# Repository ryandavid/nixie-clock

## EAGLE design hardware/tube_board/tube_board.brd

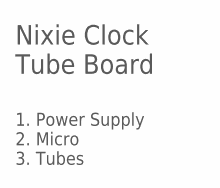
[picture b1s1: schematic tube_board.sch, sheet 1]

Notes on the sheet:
Nixie Clock Tube Board
1. Power Supply 2. Micro 3. Tubes

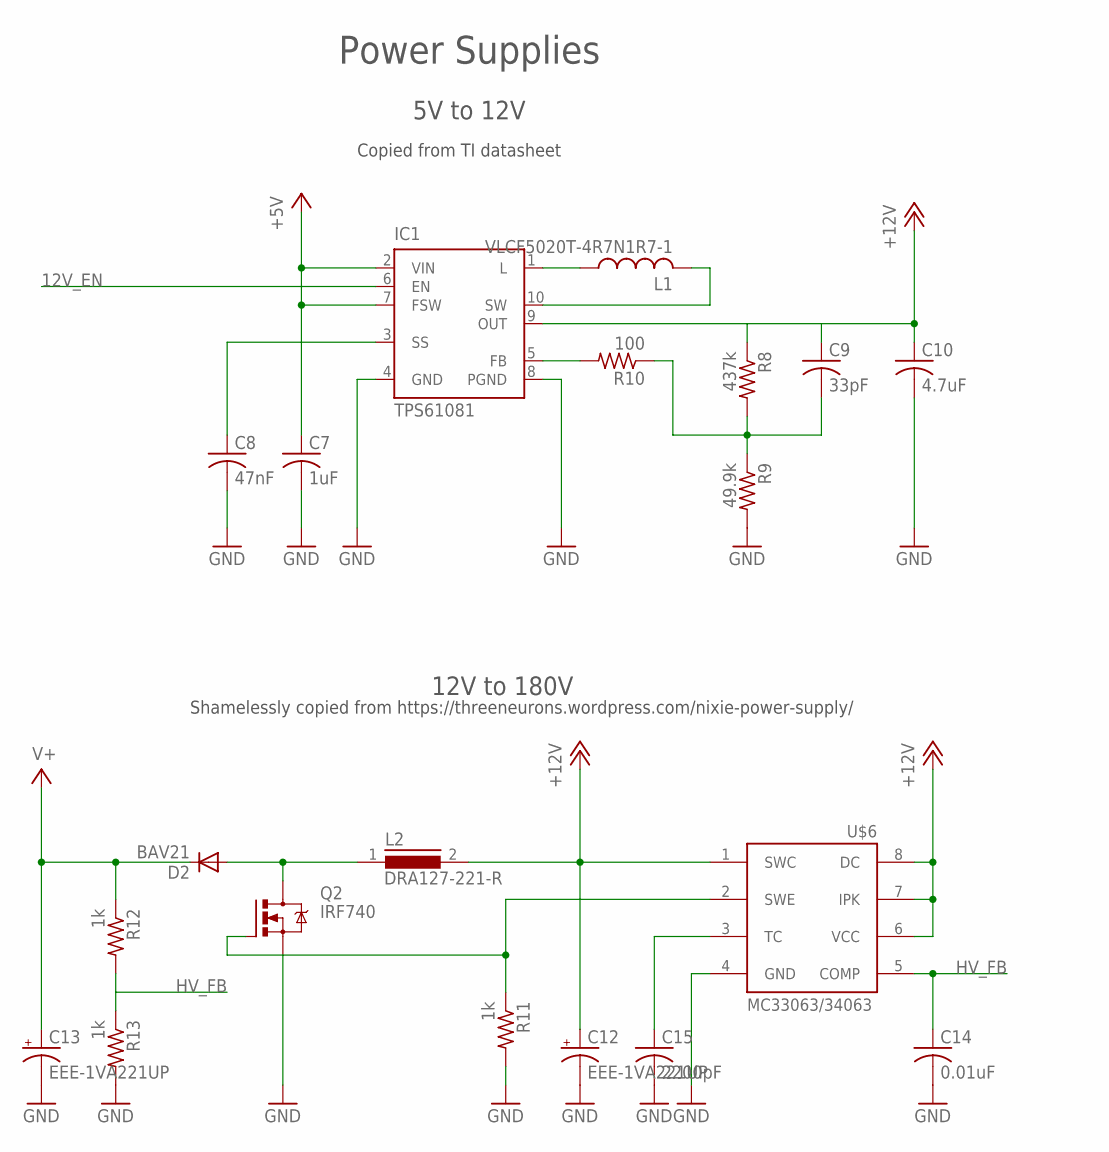
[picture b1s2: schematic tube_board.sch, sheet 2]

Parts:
C7: 1uF; C0603
C8: 47nF; C0603
C9: 33pF; C0603
C10: 4.7uF; C0603
C12, C13: EEE-1VA221UP; PANASONIC_G
C14: 0.01uF; C0603
C15: 2200pF; C0603
D2: BAV21; SOD323-R
IC1: TPS61081; S-PDSO-N10
L1: VLCF5020T-4R7N1R7-1; L5650M
L2: DRA127-221-R; DR127
Q2: IRF740; TO220BV
R8: 437k; R0603
R9: 49.9k; R0603
R10: 100; R0603
R11, R12, R13: 1k; R0603
U$6: MC34063D; SO08

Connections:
12V_EN: IC1.6 (EN); also elsewhere on the board
+5V: C7.1, IC1.2 (VIN), IC1.7 (FSW); also elsewhere on the board
+12V: C9.1, C10.1, C12.+, IC1.9 (OUT), L2.2, R8.1, U$6.1 (SWC), U$6.6 (VCC), U$6.7 (IPK), U$6.8 (DC); also elsewhere on the board
GND: C7.2, C8.2, C10.2, C12.-, C13.-, C14.2, C15.2, IC1.4 (GND), IC1.8 (PGND), Q2.S, R9.2, R11.2, R13.2, U$6.4 (GND); also elsewhere on the board
HV_FB: C14.1, R12.2, R13.1, U$6.5 (COMP)
unnamed: IC1.1 (L), L1.1
unnamed: IC1.10 (SW), L1.2
unnamed: C8.1, IC1.3 (SS)
unnamed: C9.2, R8.2, R9.1, R10.1
unnamed: D2.A, L2.1, Q2.D
unnamed: C15.1, U$6.3 (TC)
unnamed: IC1.5 (FB), R10.2
unnamed: Q2.G, R11.1, U$6.2 (SWE)
V+: C13.+, D2.C, R12.1; also elsewhere on the board

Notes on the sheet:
Power Supplies
Shamelessly copied from https://threeneurons.wordpress.com/nixie-power-supply/
12V to 180V
5V to 12V
Copied from TI datasheet

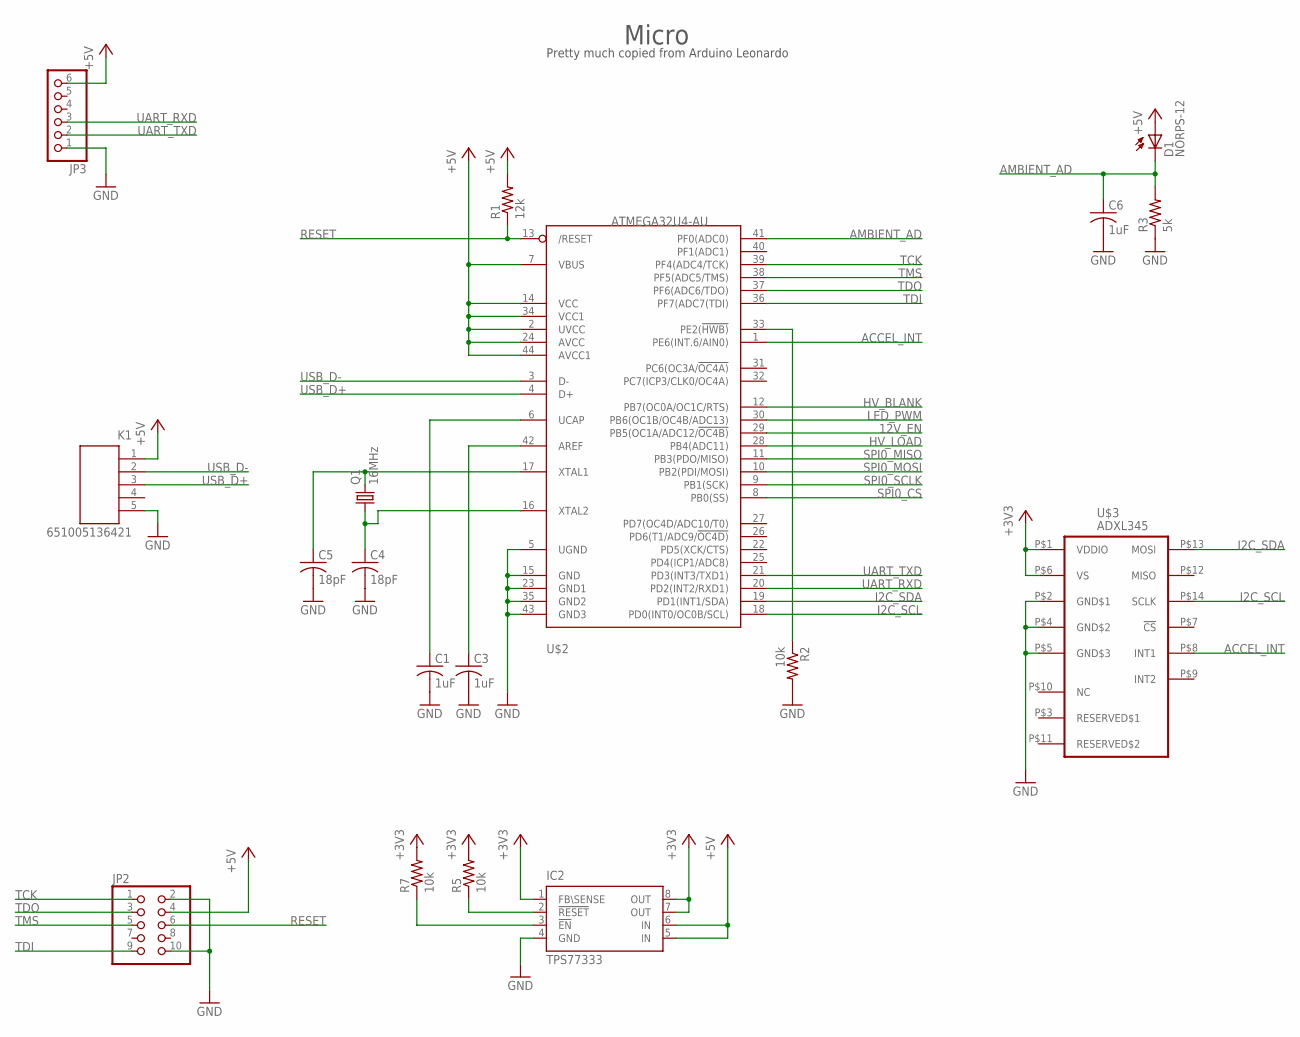
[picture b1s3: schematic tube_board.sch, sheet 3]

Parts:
C1, C3, C6: 1uF; C0603
C4, C5: 18pF; C0603
D1: NORPS-12; BPX65
IC2: TPS77333; SOP-08
JP2: PINHD-2X5; 2X05
JP3: PINHD-1X6; 1X06
K1: 651005136421
Q1: 16MHz; CTS406
R1: 12k; R0603
R2, R5, R7: 10k; R0603
R3: 5k; R0603
U$2: ATMEGA32U4-AU; TQFP44
U$3: ADXL345; LGA14

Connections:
12V_EN: U$2.29 (PB5(OC1A/ADC12/!OC4B)); also elsewhere on the board
+3V3: IC2.1 (FB\SENSE), IC2.7 (OUT), IC2.8 (OUT), R5.2, R7.2, U$3.P$1 (VDDIO), U$3.P$6 (VS)
+5V: D1.A, IC2.5 (IN), IC2.6 (IN), JP2.4, JP3.6, K1.1, R1.2, U$2.2 (UVCC), U$2.7 (VBUS), U$2.14 (VCC), U$2.24 (AVCC), U$2.34 (VCC1), U$2.44 (AVCC1); also elsewhere on the board
ACCEL_INT: U$2.1 (PE6(INT.6/AIN0)), U$3.P$8 (INT1)
AMBIENT_AD: C6.1, D1.K (C), R3.2, U$2.41 (PF0(ADC0))
GND: C1.2, C3.2, C4.2, C5.2, C6.2, IC2.4 (GND), JP2.2, JP2.10, JP3.1, K1.5, R2.2, R3.1, U$2.5 (UGND), U$2.15 (GND), U$2.23 (GND1), U$2.35 (GND2), U$2.43 (GND3), U$3.P$2 (GND$1), U$3.P$4 (GND$2), U$3.P$5 (GND$3); also elsewhere on the board
HV_BLANK: U$2.12 (PB7(OC0A/OC1C/RTS)); also elsewhere on the board
HV_LOAD: U$2.28 (PB4(ADC11)); also elsewhere on the board
I2C_SCL: U$2.18 (PD0(INT0/OC0B/SCL)), U$3.P$14 (SCLK)
I2C_SDA: U$2.19 (PD1(INT1/SDA)), U$3.P$13 (MOSI)
LED_PWM: U$2.30 (PB6(OC1B/OC4B/ADC13)); also elsewhere on the board
unnamed: IC2.2 (!RESET), R5.1
unnamed: C1.1, U$2.6 (UCAP)
unnamed: C3.1, U$2.42 (AREF)
unnamed: C5.1, Q1.3 (2), U$2.17 (XTAL1)
unnamed: C4.1, Q1.1, U$2.16 (XTAL2)
unnamed: R2.1, U$2.33 (PE2(!HWB))
unnamed: IC2.3 (!EN), R7.1
RESET: JP2.6, R1.1, U$2.13 (/RESET)
SPI0_CS: U$2.8 (PB0(SS))
SPI0_MISO: U$2.11 (PB3(PDO/MISO))
SPI0_MOSI: U$2.10 (PB2(PDI/MOSI)); also elsewhere on the board
SPI0_SCLK: U$2.9 (PB1(SCK)); also elsewhere on the board
TCK: JP2.1, U$2.39 (PF4(ADC4/TCK))
TDI: JP2.9, U$2.36 (PF7(ADC7(TDI))
TDO: JP2.3, U$2.37 (PF6(ADC6/TDO))
TMS: JP2.5, U$2.38 (PF5(ADC5/TMS))
UART_RXD: JP3.3, U$2.20 (PD2(INT2/RXD1))
UART_TXD: JP3.2, U$2.21 (PD3(INT3/TXD1))
USB_D+: K1.3, U$2.4 (D+)
USB_D-: K1.2, U$2.3 (D-)

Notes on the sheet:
Micro
Pretty much copied from Arduino Leonardo

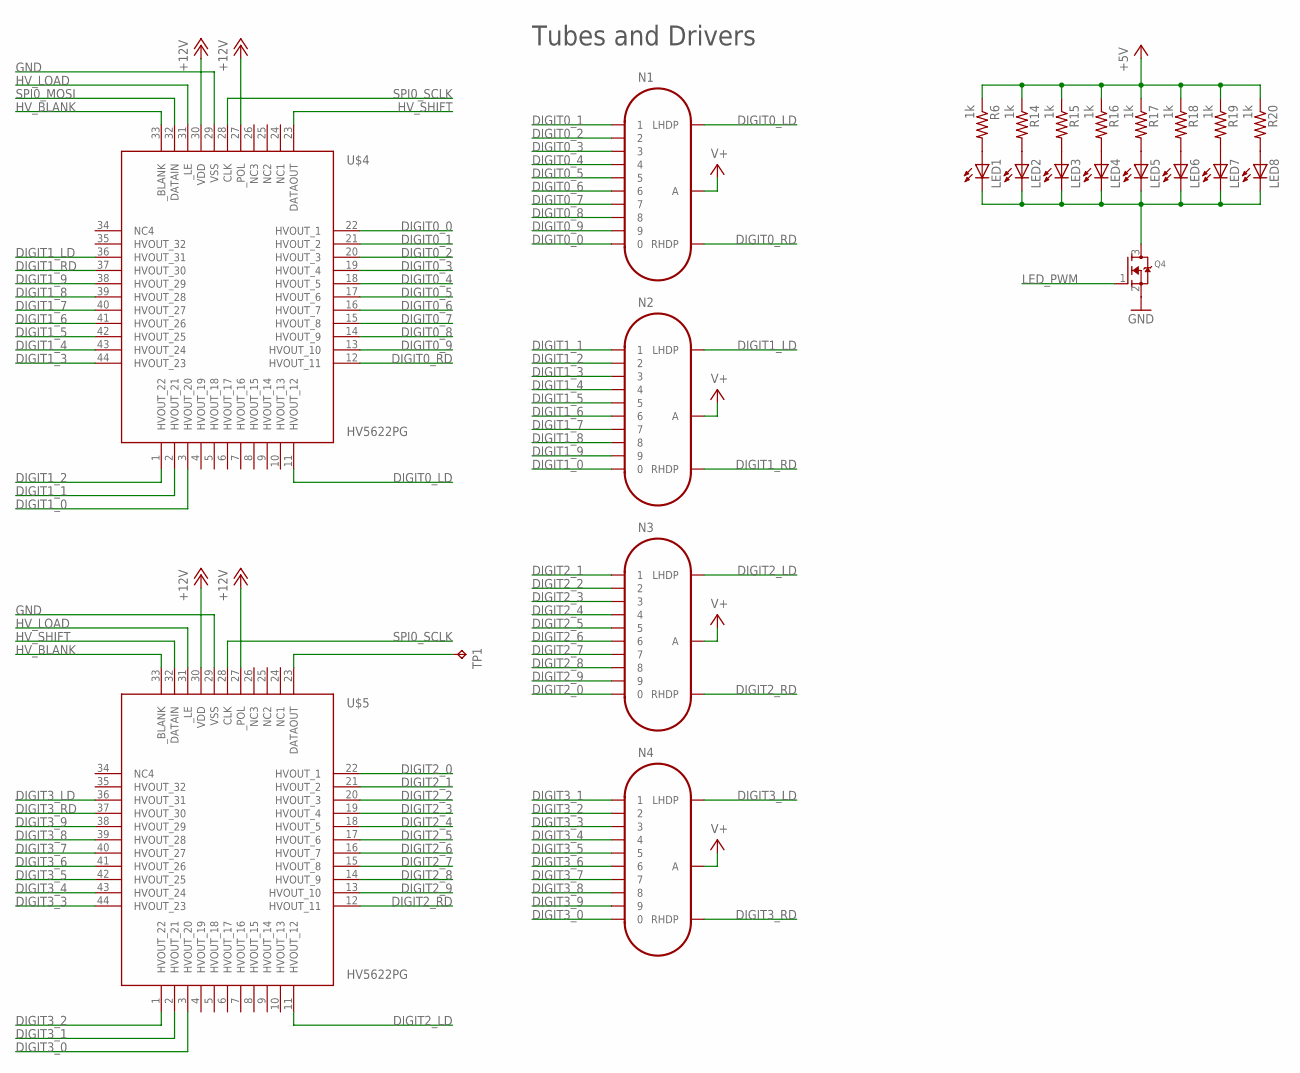
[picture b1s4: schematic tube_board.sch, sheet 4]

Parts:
LED1, LED2, LED3, LED4, LED5, LED6, LED7, LED8: LEDCHIPLED_0603; CHIPLED_0603
N1, N2, N3, N4: IN-14SMD; IN-14-SMD
Q4: MOSFET-NREFLOW; SOT23
R6, R14, R15, R16, R17, R18, R19, R20: 1k; R0603
TP1: TPTP07R; TP07R
U$4, U$5: HV5622PG; PQFP-44

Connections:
+5V: R6.1, R14.1, R15.1, R16.1, R17.1, R18.1, R19.1, R20.1; also elsewhere on the board
+12V: U$4.30 (VDD), U$5.27 (_POL), U$5.30 (VDD); also elsewhere on the board
DIGIT0_0: N1.0, U$4.22 (HVOUT_1)
DIGIT0_1: N1.1, U$4.21 (HVOUT_2)
DIGIT0_2: N1.2, U$4.20 (HVOUT_3)
DIGIT0_3: N1.3, U$4.19 (HVOUT_4)
DIGIT0_4: N1.4, U$4.18 (HVOUT_5)
DIGIT0_5: N1.5, U$4.17 (HVOUT_6)
DIGIT0_6: N1.6, U$4.16 (HVOUT_7)
DIGIT0_7: N1.7, U$4.15 (HVOUT_8)
DIGIT0_8: N1.8, U$4.14 (HVOUT_9)
DIGIT0_9: N1.9, U$4.13 (HVOUT_10)
DIGIT0_LD: N1.LHDP, U$4.11 (HVOUT_12)
DIGIT0_RD: N1.RHDP, U$4.12 (HVOUT_11)
DIGIT1_0: N2.0, U$4.3 (HVOUT_20)
DIGIT1_1: N2.1, U$4.2 (HVOUT_21)
DIGIT1_2: N2.2, U$4.1 (HVOUT_22)
DIGIT1_3: N2.3, U$4.44 (HVOUT_23)
DIGIT1_4: N2.4, U$4.43 (HVOUT_24)
DIGIT1_5: N2.5, U$4.42 (HVOUT_25)
DIGIT1_6: N2.6, U$4.41 (HVOUT_26)
DIGIT1_7: N2.7, U$4.40 (HVOUT_27)
DIGIT1_8: N2.8, U$4.39 (HVOUT_28)
DIGIT1_9: N2.9, U$4.38 (HVOUT_29)
DIGIT1_LD: N2.LHDP, U$4.36 (HVOUT_31)
DIGIT1_RD: N2.RHDP, U$4.37 (HVOUT_30)
DIGIT2_0: N3.0, U$5.22 (HVOUT_1)
DIGIT2_1: N3.1, U$5.21 (HVOUT_2)
DIGIT2_2: N3.2, U$5.20 (HVOUT_3)
DIGIT2_3: N3.3, U$5.19 (HVOUT_4)
DIGIT2_4: N3.4, U$5.18 (HVOUT_5)
DIGIT2_5: N3.5, U$5.17 (HVOUT_6)
DIGIT2_6: N3.6, U$5.16 (HVOUT_7)
DIGIT2_7: N3.7, U$5.15 (HVOUT_8)
DIGIT2_8: N3.8, U$5.14 (HVOUT_9)
DIGIT2_9: N3.9, U$5.13 (HVOUT_10)
DIGIT2_LD: N3.LHDP, U$5.11 (HVOUT_12)
DIGIT2_RD: N3.RHDP, U$5.12 (HVOUT_11)
DIGIT3_0: N4.0, U$5.3 (HVOUT_20)
DIGIT3_1: N4.1, U$5.2 (HVOUT_21)
DIGIT3_2: N4.2, U$5.1 (HVOUT_22)
DIGIT3_3: N4.3, U$5.44 (HVOUT_23)
DIGIT3_4: N4.4, U$5.43 (HVOUT_24)
DIGIT3_5: N4.5, U$5.42 (HVOUT_25)
DIGIT3_6: N4.6, U$5.41 (HVOUT_26)
DIGIT3_7: N4.7, U$5.40 (HVOUT_27)
DIGIT3_8: N4.8, U$5.39 (HVOUT_28)
DIGIT3_9: N4.9, U$5.38 (HVOUT_29)
DIGIT3_LD: N4.LHDP, U$5.36 (HVOUT_31)
DIGIT3_RD: N4.RHDP, U$5.37 (HVOUT_30)
GND: Q4.2 (S), U$4.29 (VSS), U$5.29 (VSS); also elsewhere on the board
HV_BLANK: U$4.33 (_BLANK), U$5.33 (_BLANK); also elsewhere on the board
HV_LOAD: U$4.31 (_LE), U$5.31 (_LE); also elsewhere on the board
HV_SHIFT: U$4.23 (DATAOUT), U$5.32 (DATAIN)
LED_PWM: Q4.1 (G); also elsewhere on the board
unnamed: LED1.A, R6.2
unnamed: LED2.A, R14.2
unnamed: LED3.A, R15.2
unnamed: LED4.A, R16.2
unnamed: LED5.A, R17.2
unnamed: LED6.A, R18.2
unnamed: LED7.A, R19.2
unnamed: LED8.A, R20.2
unnamed: LED1.C, LED2.C, LED3.C, LED4.C, LED5.C, LED6.C, LED7.C, LED8.C, Q4.3 (D)
unnamed: TP1.TP, U$5.23 (DATAOUT)
SPI0_MOSI: U$4.32 (DATAIN); also elsewhere on the board
SPI0_SCLK: U$4.28 (CLK), U$5.28 (CLK); also elsewhere on the board
V+: N1.A, N2.A, N3.A, N4.A; also elsewhere on the board

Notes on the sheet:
Tubes and Drivers

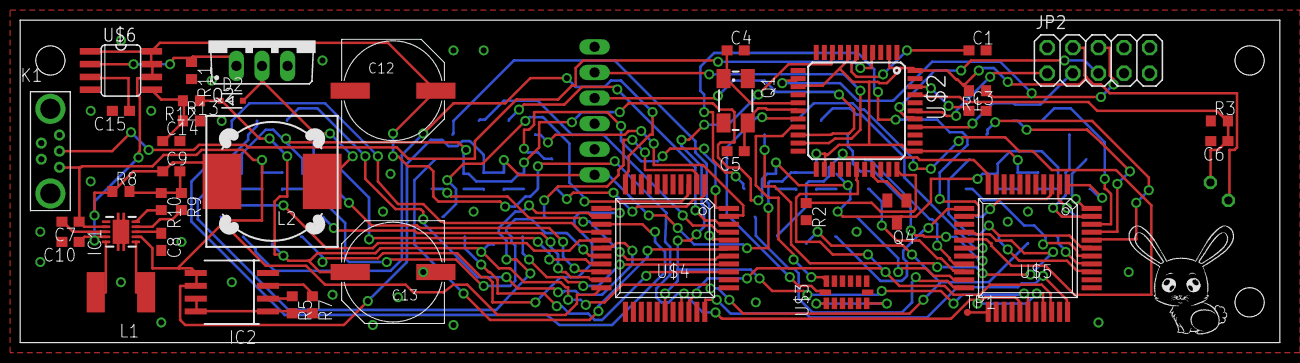
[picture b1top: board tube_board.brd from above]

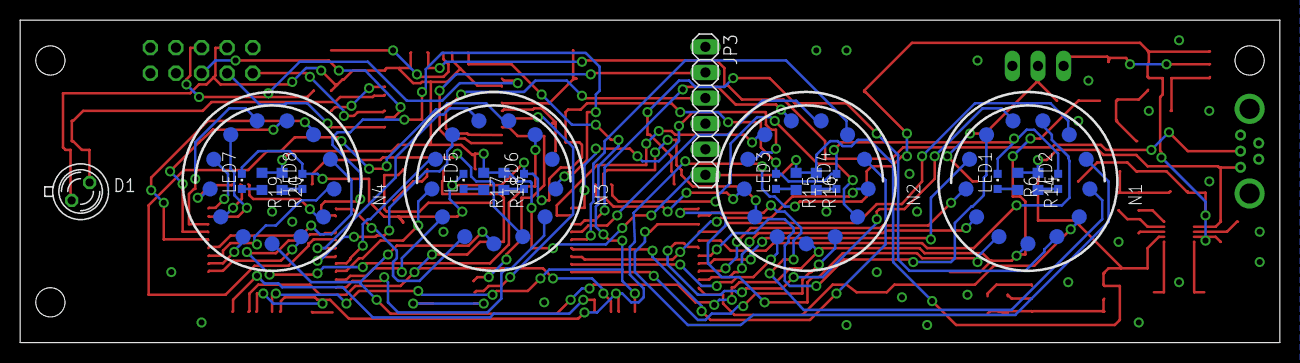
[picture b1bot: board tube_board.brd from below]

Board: 2 copper layers, 125.0 x 32.0 mm, 62 parts (22 on the bottom side), 99 nets.

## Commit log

2017-04-28 Finish first draft of schematic
2017-05-01 Finish schematic and start board layout
2017-05-22 WIP board layout
2017-08-05 Hacky autorouted board

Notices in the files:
parts and their libraries:
Wuerth_Elektronik_eiCan_Communication_Co: Copyright: Würth Elektronik
